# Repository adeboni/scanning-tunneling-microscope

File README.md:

# Home-made scanning tunneling microscope

This repository contains schematics I made in order to fully build Dan Berard's STM implementation, based on John Alexander's STM design: https://dberard.com/home-built-stm/

## Sample scan from the STM:

## Pictures of the STM:

## SEM image of the probe tip:

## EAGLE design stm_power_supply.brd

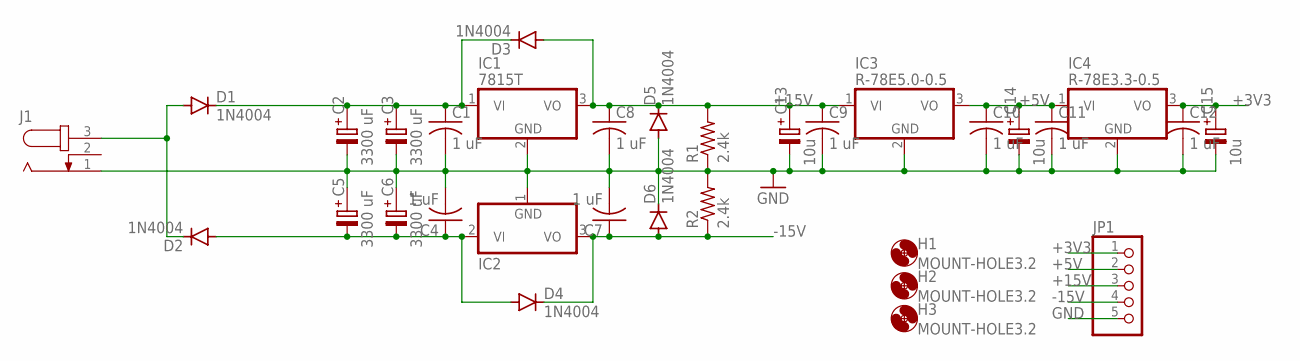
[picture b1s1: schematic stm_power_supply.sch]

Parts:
C1, C4, C7, C8, C9, C10, C11, C12: 1 uF; C025-024X044
C2, C3, C5, C6: 3300 uF; E7,5-18
C13, C14, C15: 10u; E2,5-6
D1, D2, D3, D4, D5, D6: 1N4004; DO41-10
H1, H2, H3: MOUNT-HOLE3.2; 3,2
IC1: 7815T; TO220H
IC2: 7915T; TO220H
IC3: R-78E5.0-0.5; WE78
IC4: R-78E3.3-0.5; WE78
J1: JACK-PLUG0; SPC4077
JP1: PINHD-1X5; 1X05
R1, R2: 2.4k; 0204/7

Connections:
+3V3: C12.1, C15.+, IC4.3 (VO), JP1.1
+5V: C10.1, C11.1, C14.+, IC3.3 (VO), IC4.1 (VI), JP1.2
+15V: C8.1, C9.1, C13.+, D3.A, D5.C, IC1.3 (VO), IC3.1 (VI), JP1.3, R1.2
-15V: C7.1, D4.C, D6.A, IC2.3 (VO), JP1.4, R2.1
GND: C1.2, C2.-, C3.-, C4.2, C5.+, C6.+, C7.2, C8.2, C9.2, C10.2, C11.2, C12.2, C13.-, C14.-, C15.-, D5.A, D6.C, IC1.2 (GND), IC2.1 (GND), IC3.2 (GND), IC4.2 (GND), J1.1, JP1.5, R1.1, R2.2
unnamed: C1.1, C2.+, C3.+, D1.C, D3.C, IC1.1 (VI)
unnamed: D1.A, D2.C, J1.3
unnamed: C4.1, C5.-, C6.-, D2.A, D4.A, IC2.2 (VI)

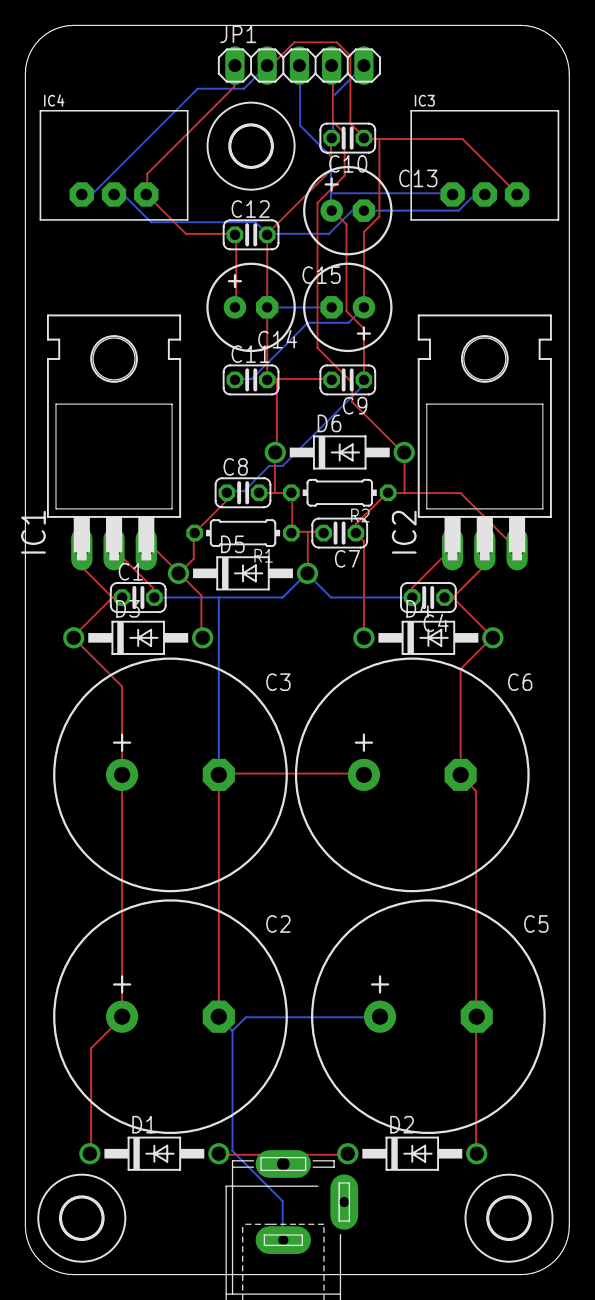
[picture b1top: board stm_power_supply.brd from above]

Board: 2 copper layers, 42.9 x 98.4 mm, 32 parts (0 on the bottom side), 8 nets.

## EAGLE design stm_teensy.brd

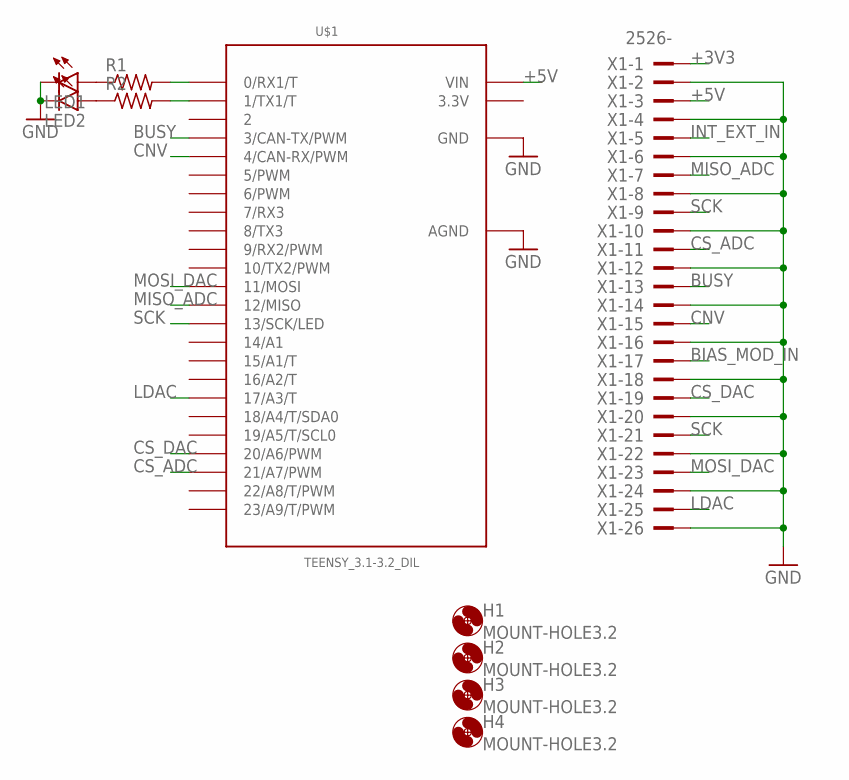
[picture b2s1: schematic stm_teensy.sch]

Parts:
H1, H2, H3, H4: MOUNT-HOLE3.2; 3,2
LED1, LED2: LED5MM
R1, R2: R-US_0204/7; 0204/7
U$1: TEENSY_3.1-3.2_DIL; TEENSY_3.0-3.2&LC_DIL
X1: 2526-; PAK100/2500-26

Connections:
3.3V: U$1.3.3V
+3V3: X1.1
+5V: U$1.VIN, X1.3
BIAS_MOD_IN: X1.17
BUSY: U$1.3 (3/CAN-TX/PWM), X1.13
CNV: U$1.4 (4/CAN-RX/PWM), X1.15
CS_ADC: U$1.21/A7 (21/A7/PWM), X1.11
CS_DAC: U$1.20/A6 (20/A6/PWM), X1.19
GND: LED1.K (C), LED2.K (C), U$1.AGND, U$1.GND, X1.2, X1.4, X1.6, X1.8, X1.10, X1.12, X1.14, X1.16, X1.18, X1.20, X1.22, X1.24, X1.26
INT_EXT_IN: X1.5
LDAC: U$1.17/A3 (17/A3/T), X1.25
MISO_ADC: U$1.12 (12/MISO), X1.7
MOSI_DAC: U$1.11 (11/MOSI), X1.23
unnamed: LED1.A, R1.1
unnamed: LED2.A, R2.1
unnamed: R1.2, U$1.0 (0/RX1/T)
unnamed: R2.2, U$1.1 (1/TX1/T)
SCK: U$1.13 (13/SCK/LED), X1.9, X1.21

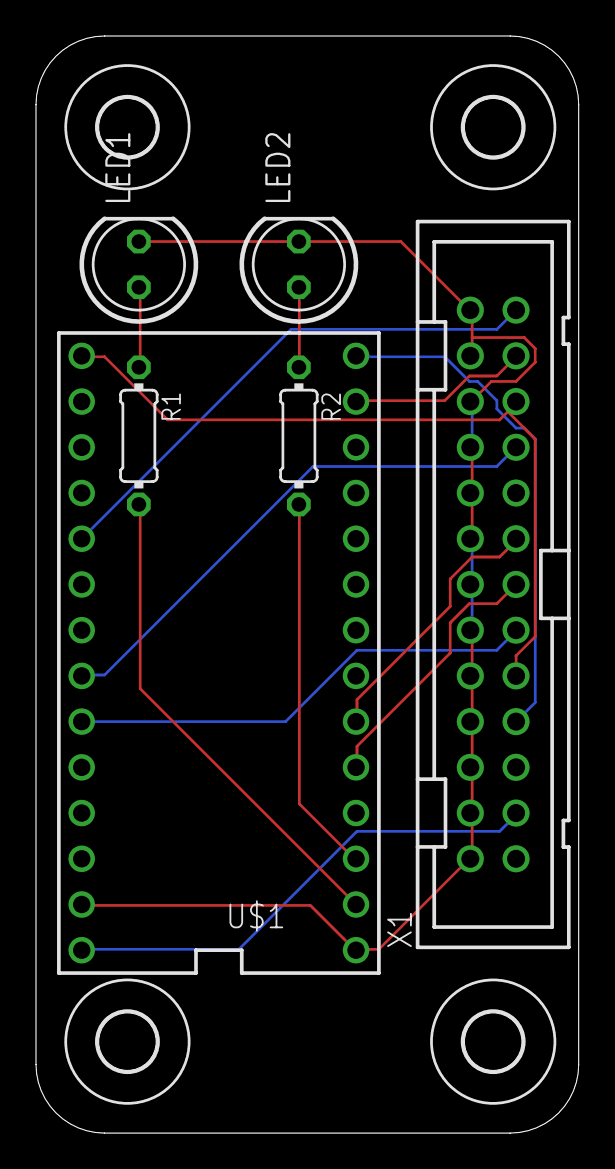
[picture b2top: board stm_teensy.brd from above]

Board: 2 copper layers, 30.1 x 61.0 mm, 10 parts (0 on the bottom side), 14 nets.

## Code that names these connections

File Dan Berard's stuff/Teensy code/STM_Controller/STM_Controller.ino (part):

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
All GNDs -> Teensy GND
+5V -> Vin
~CS_DAC -> pin 20
~LDAC -> pin 17
~CS_ADC -> pin 21
CNV -> pin 4
BUSY -> pin 3
MISO_ADC -> pin 12
MOSI_DAC -> pin 11
Serial indicator LED -> pin 0
Tunneling indicator LED -> pin 1
SCK_ADC and SCK_DAC -> pin 13.
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

// Pin definitions:
#define CS_DAC 20                          // DAC chip select pin
#define LDAC 17                            // Load DAC pin, not currently used
#define CS_ADC 21                          // ADC chip select pin
#define CNV 4                              // ADC CNV pin - initiates a conversion
#define BUSY 3                             // ADC BUSY pin
#define SERIAL_LED 0                       // Indicates serial data transmission
#define TUNNEL_LED 1                       // Indicates tunneling
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
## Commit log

2020-07-09 Initial check-in
2020-08-06 added more files
2020-08-06 Added image to readme
2020-08-07 added device photos
2020-08-07 added tip photo
2020-08-07 updated tip photo

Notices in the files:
Dan Berard's stuff/Teensy code/STM_Controller/STM_Controller.ino:
Copyright (c) Daniel Berard, daniel.berard@mail.mcgill.ca
parts and their libraries:
cap-pan40: Copyright (C) 2004, Bob Starr
